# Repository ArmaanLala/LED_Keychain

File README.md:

# LED Keychain

Press a button to active a few SMD leds

rev# marks an existing PCB that has been ordered and purchased. After a rev# is submitted and purchased that revision will not be edited anymore and the next revision will be started. The current revision is rev2

#### Important links

Battery Holder
https://www.digikey.com/en/products/detail/keystone-electronics/3035/5872907?s=N4IgTCBcDaINYFMCeBnALgewHYIAQGYAGfAVhAF0BfIA

LEDs
https://www.sparkfun.com/products/10866

Keyboard switch
https://kbdfans.com/collections/kailh-switches/products/novelkeys-x-kailh-box-thick-clicks-navy-jade

## Schematic and Board layout

Schematic view

Layout view

Board view

##
LED Componets
AA1608SURSK
AA1608SYSK
AA1608CGSK

## Credits

This Eagle project is a personal collaboration project between Armaan Lala and Peter Chu.

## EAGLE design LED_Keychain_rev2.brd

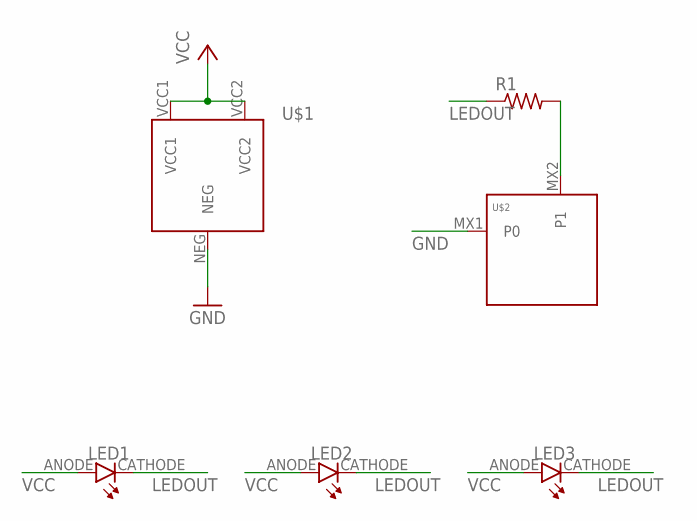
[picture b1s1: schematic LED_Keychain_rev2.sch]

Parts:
LED1, LED2, LED3: KINGBRIGHT-A1608; KINGBRIGHT-0603
R1: R-US_R0603; R0603
U$1: KEYSTONE3035
U$2: KEYSWITCH-PLAIN-MX-1U; MX-1U

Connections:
GND: U$1.NEG, U$2.MX1 (P0)
LEDOUT: LED1.CATHODE, LED2.CATHODE, LED3.CATHODE, R1.1
unnamed: R1.2, U$2.MX2 (P1)
VCC: LED1.ANODE, LED2.ANODE, LED3.ANODE, U$1.VCC1, U$1.VCC2

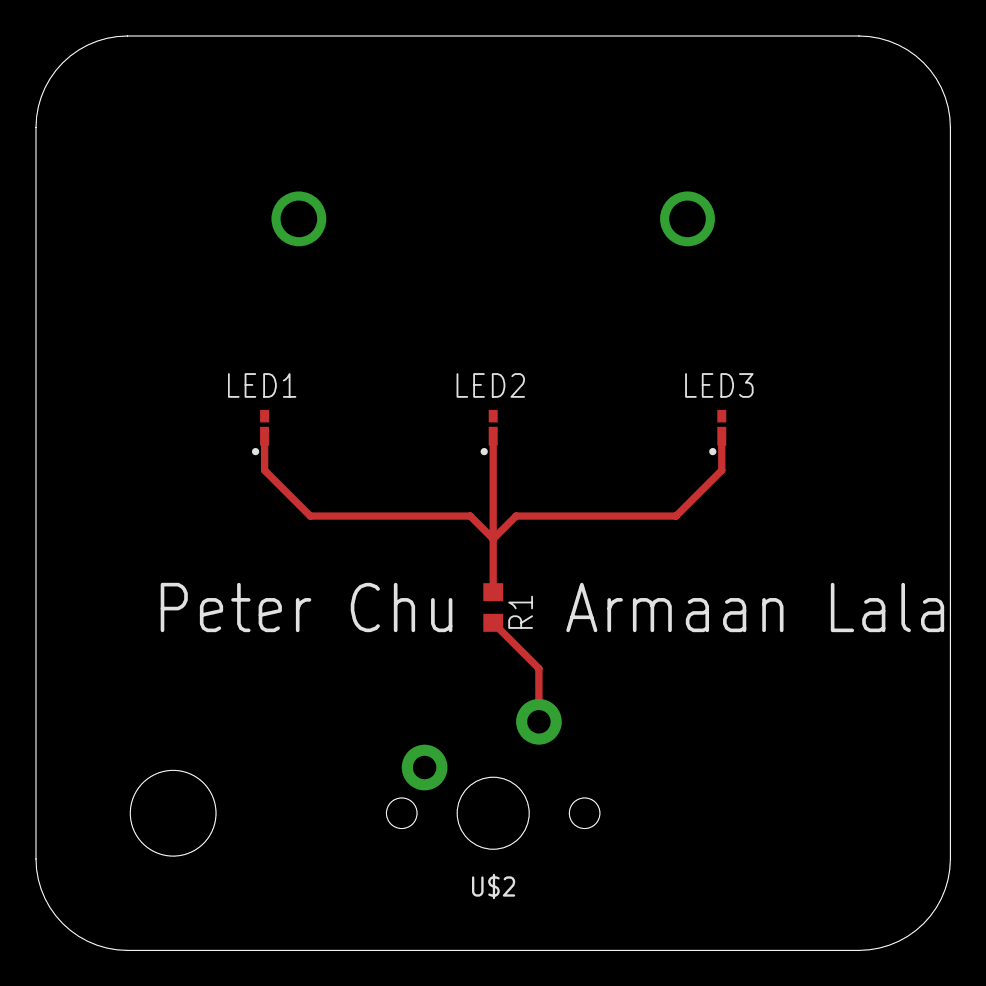
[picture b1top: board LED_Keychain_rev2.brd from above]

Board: 2 copper layers, 50.8 x 50.8 mm, 6 parts (1 on the bottom side), 4 nets.

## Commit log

2021-01-18 added README
2021-01-18 Added empty EAGLE board and Schematic
2021-01-18 Added Key switch and updated readme
2021-01-18 Added key switches
2021-01-19 Added gitignore for Eagle save files
2021-01-19 Modified gitignore to ignore respsitory related files
2021-01-19 Added Keystone3035 in LED_Keychain_lib.lbr.
2021-01-19 Added Datasheet and made board changes
2021-01-21 Layed out the board and finished the schematic
2021-01-21 Updated README with images and documentation
2021-01-21 Rounded edges and better silkscreen
2021-01-26 Added gerber files
2021-04-08 Starting rev2 to LED_Keychain
2021-04-13 Added functional rev2
2021-04-13 Changed readme
2021-11-10 Created readme.md
2021-11-10 Undo accidental edit
